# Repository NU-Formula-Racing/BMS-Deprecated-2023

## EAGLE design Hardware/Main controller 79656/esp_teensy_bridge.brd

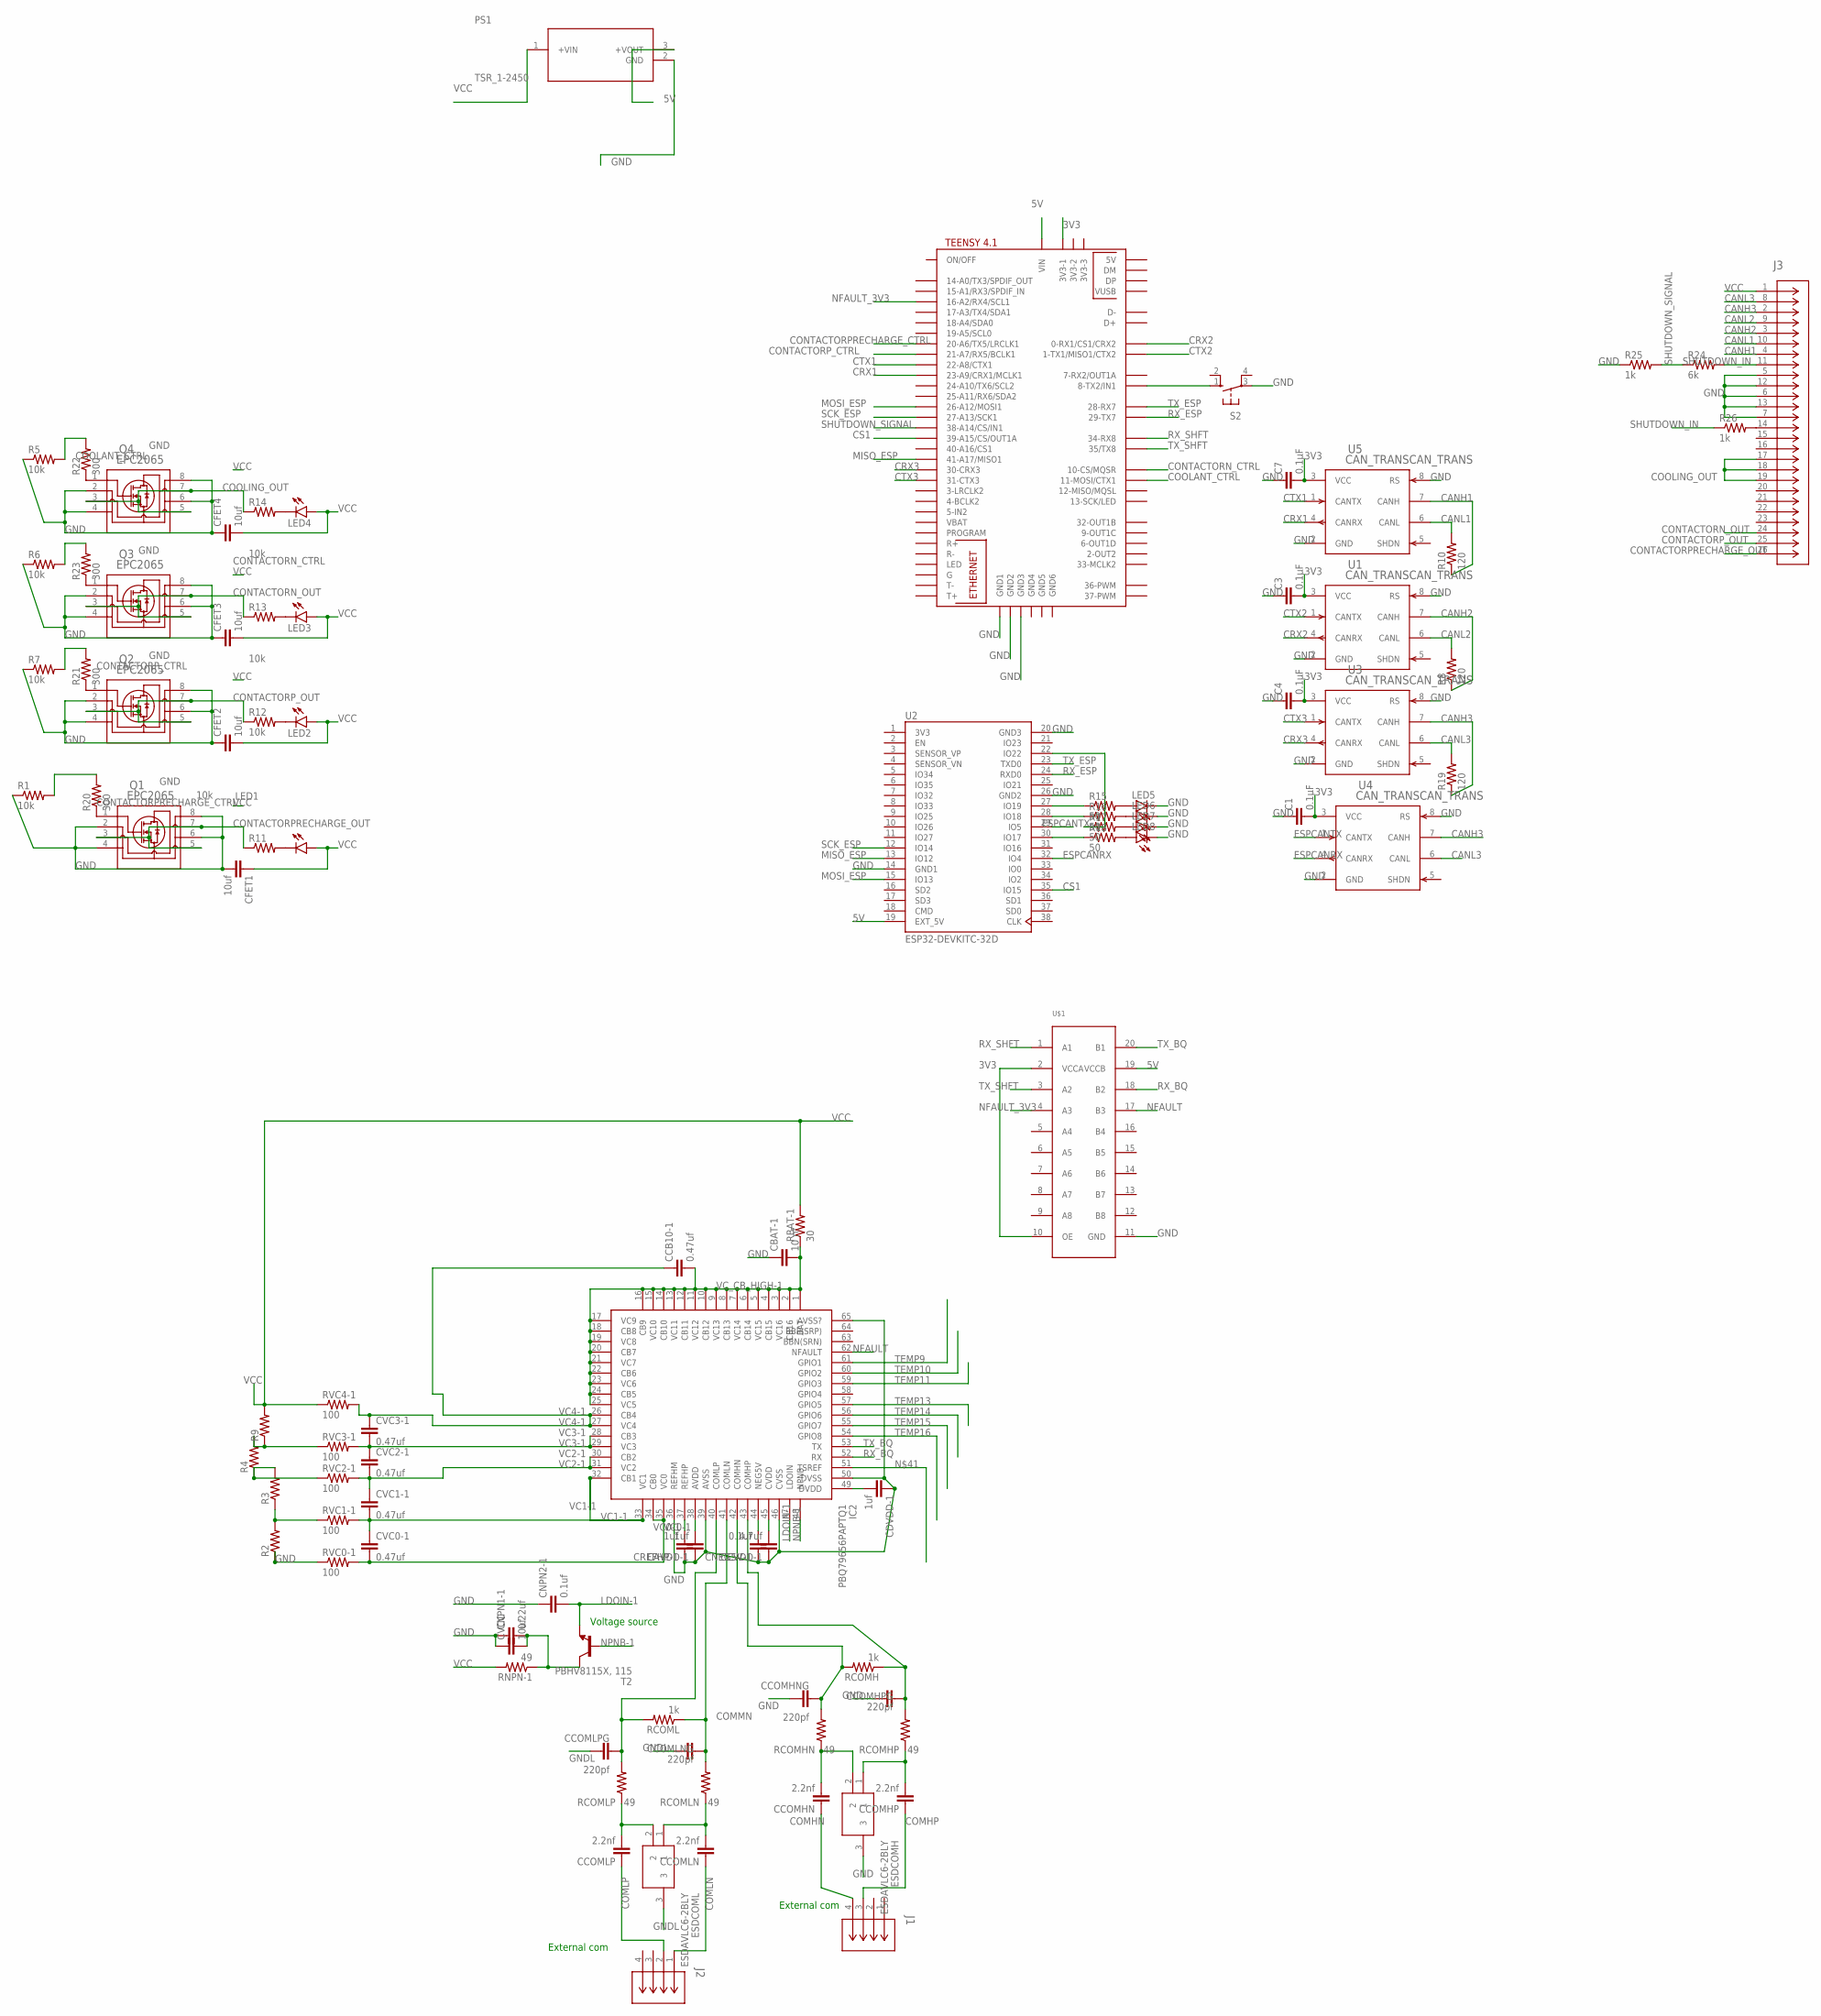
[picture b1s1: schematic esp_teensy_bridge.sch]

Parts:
C1, C3, C4, C7: 0.1μF; C0603
CAVDD-1: 1uf; C0603
CBAT-1: 10 nf; C0603
CCB10-1: 0.47uf; C0603
CCOMHN: 2.2nf; C075-032X103
CCOMHNG: 220pf; C0603
CCOMHP: 2.2nf; C075-032X103
CCOMHPG: 220pf; C0603
CCOMLN: 2.2nf; C075-032X103
CCOMLNG: 220pf; C0603
CCOMLP: 2.2nf; C075-032X103
CCOMLPG: 220pf; C0603
CCVDD-1: 4.7uf; C0603
CDVDD-1: 1uf; C0603
CFET1, CFET2, CFET3, CFET4: 10uf; C0805
CNEG5V-1: 0.1uf; C0603
CNPN1-1: 0.22uf; C0603
CNPN2-1: 0.1uf; C0603
CREFHP-1: 1uf; C0603
CVC0-1, CVC1-1, CVC2-1, CVC3-1: 0.47uf; C0603
CVCC: 10uf; C0805
ESDCOMH: ESDAVLC6-2BLY; SOT95P255X150-3N
ESDCOML: ESDAVLC6-2BLY; SOT95P255X150-3N
IC2: PBQ79656PAPTQ1; QFP50P1200X1200X120-65N
J1, J2: DF11-4DP-2DSA(24); CON4_2X2_UF_DF11_HIR
J3: TE_AMP_SURESEAL_26; CONN26_6473423-1_TEC
LED1, LED2, LED3, LED4, LED5, LED6, LED7, LED8: LEDSML0603; SML0603
PS1: TSR_1-2450; TSR1-SINGLE_TRP
Q1, Q2, Q3, Q4: EPC2065; EPC2065_ECC
R1, R5, R6, R7, R11, R12, R13, R14: 10k; R0603
R2, R3, R4, R9: R-US_R0805; R0805
R8, R10, R19: 120; R0603
R15, R16, R17, R18: 50; R0603
R20, R21, R22, R23: 300; R0603
R24: 6k; R0603
R25, R26: 1k; R0603
RBAT-1: 30; R0603
RCOMH: 1k; R0603
RCOMHN: 49; R0603
RCOMHP: 49; R0603
RCOML: 1k; R0603
RCOMLN: 49; R0603
RCOMLP: 49; R0603
RNPN-1: 49; R0603
RVC0-1, RVC1-1, RVC2-1, RVC3-1, RVC4-1: 100; R0603
S2: 10-XX; B3F-10XX
T2: PBHV8115X, 115; SOT89-BCE
U1, U3, U4, U5: CAN_TRANSCAN_TRANS; MAX3051ESA+
U2: ESP32-DEVKITC-32D; MODULE_ESP32-DEVKITC-32D
U$1: TXB0108PWSMD; TSSOP20
U$3: TEENSY41

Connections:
3V3: C1.2, C3.2, C4.2, C7.2, U1.3 (VCC), U2.1 (3V3), U3.3 (VCC), U4.3 (VCC), U5.3 (VCC), U$1.2 (VCCA), U$1.10 (OE), U$3.3V3-1
5V: PS1.3 (+VOUT), U2.19 (EXT_5V), U$1.19 (VCCB), U$3.VIN
CANH1: J3.4, R10.1, U5.7 (CANH)
CANH2: J3.3, R8.1, U1.7 (CANH)
CANH3: J3.2, R19.1, U3.7 (CANH), U4.7 (CANH)
CANL1: J3.10, R10.2, U5.6 (CANL)
CANL2: J3.9, R8.2, U1.6 (CANL)
CANL3: J3.8, R19.2, U3.6 (CANL), U4.6 (CANL)
COMHN: CCOMHN.1, J1.4
COMHP: CCOMHP.1, J1.3
COMLN: CCOMLN.1, J2.1
COMLP: CCOMLP.1, J2.2
CONTACTORN_CTRL: R6.2, R23.2, U$3.10-CS\MQSR (10-CS/MQSR)
CONTACTORN_OUT: J3.24, Q3.3, Q3.5, Q3.7, R13.1
CONTACTORPRECHARGE_CTRL: R1.2, R20.2, U$3.20-A6/TX5/LRCLK1
CONTACTORPRECHARGE_OUT: J3.26, Q1.3, Q1.5, Q1.7, R11.1
CONTACTORP_CTRL: R7.2, R21.2, U$3.21-A7/RX5/BCLK1
CONTACTORP_OUT: J3.25, Q2.3, Q2.5, Q2.7, R12.1
COOLANT_CTRL: R5.2, R22.2, U$3.11-MOSI/CTX1
COOLING_OUT: J3.17, J3.18, J3.19, Q4.3, Q4.5, Q4.7, R14.1
CRX1: U5.4 (CANRX), U$3.23-A9/CRX1/MCLK1
CRX2: U1.4 (CANRX), U$3.0-RX1/CS1/CRX2
CRX3: U3.4 (CANRX), U$3.30-CRX3
CS1: U2.35 (IO15), U$3.39-A15/CS/OUT1A
CTX1: U5.1 (CANTX), U$3.22-A8/CTX1
CTX2: U1.1 (CANTX), U$3.1-TX1/MISO1/CTX2
CTX3: U3.1 (CANTX), U$3.31-CTX3
CVDD-1: CCVDD-1.2, IC2.45 (CVDD)
ESPCANRX: U2.32 (IO4), U4.4 (CANRX)
ESPCANTX: U2.29 (IO5), U4.1 (CANTX)
GND: C1.1, C3.1, C4.1, C7.1, CAVDD-1.1, CBAT-1.1, CCOMHNG.1, CCOMHPG.1, CCVDD-1.1, CDVDD-1.1, CFET1.2, CFET2.1, CFET3.1, CFET4.1, CNEG5V-1.1, CNPN1-1.1, CNPN2-1.1, CREFHP-1.1, CVCC.1, ESDCOMH.3, IC2.36 (REFHM), IC2.39 (AVSS), IC2.46 (CVSS), IC2.50 (DVSS), IC2.65 (AVSS?), J3.5, J3.6, J3.7, J3.12, J3.13, LED5.C, LED6.C, LED7.C, LED8.C, PS1.2 (GND), Q1.2, Q1.4, Q1.6, Q1.8, Q2.2, Q2.4, Q2.6, Q2.8, Q3.2, Q3.4, Q3.6, Q3.8, Q4.2, Q4.4, Q4.6, Q4.8, R1.1, R2.1, R5.1, R6.1, R7.1, R25.1, RVC0-1.1, S2.3, U1.2 (GND), U1.8 (RS), U2.14 (GND1), U2.20 (GND3), U2.26 (GND2), U3.2 (GND), U3.8 (RS), U4.2 (GND), U4.8 (RS), U5.2 (GND), U5.8 (RS), U$1.11 (GND), U$3.GND1, U$3.GND2, U$3.GND3
GNDL: CCOMLNG.1, CCOMLPG.1, ESDCOML.3
LDOIN-1: CNPN2-1.2, IC2.47 (LDOIN), T2.E
MISO_ESP: U2.13 (IO12), U$3.41-A17/MISO1
MOSI_ESP: U2.15 (IO13), U$3.26-A12/MOSI1
unnamed: CCOMHP.2, ESDCOMH.1, RCOMHP.1
unnamed: J3.14, R26.2
unnamed: LED4.C, R14.2
unnamed: LED3.C, R13.2
unnamed: S2.1 (S), U$3.8-TX2/IN1
unnamed: CCOMHN.2, ESDCOMH.2, RCOMHN.1
unnamed: LED2.C, R12.2
unnamed: CCOMLNG.2, IC2.41 (COMLN), RCOML.1, RCOMLN.2
unnamed: R17.1, U2.22 (IO22)
unnamed: LED1.C, R11.2
unnamed: Q1.1, R20.1
unnamed: Q2.1, R21.1
unnamed: R15.1, U2.27 (IO19)
unnamed: R16.1, U2.28 (IO18)
unnamed: Q3.1, R23.1
unnamed: R18.1, U2.30 (IO17)
unnamed: LED5.A, R15.2
unnamed: LED6.A, R16.2
unnamed: LED7.A, R17.2
unnamed: LED8.A, R18.2
unnamed: Q4.1, R22.1
unnamed: CCOMLPG.2, IC2.40 (COMLP), RCOML.2, RCOMLP.2
unnamed: CCOMLP.2, ESDCOML.2, RCOMLP.1
unnamed: CCOMLN.2, ESDCOML.1, RCOMLN.1
unnamed: R3.2, R4.1, RVC2-1.1
unnamed: R2.2, R3.1, RVC1-1.1
unnamed: R4.2, R9.1, RVC3-1.1
unnamed: CREFHP-1.2, IC2.37 (REFHP)
unnamed: CAVDD-1.2, IC2.38 (AVDD)
unnamed: CNEG5V-1.2, IC2.44 (NEG5V)
unnamed: CDVDD-1.2, IC2.49 (DVDD)
unnamed: CNPN1-1.2, CVCC.2, RNPN-1.1, T2.C
unnamed: CCOMHPG.2, IC2.43 (COMHP), RCOMH.1, RCOMHP.2
unnamed: CCOMHNG.2, IC2.42 (COMHN), RCOMH.2, RCOMHN.2
NFAULT: IC2.62 (NFAULT), U$1.17 (B3)
NFAULT_3V3: U$1.4 (A3), U$3.16-A2/RX4/SCL1
NPNB-1: IC2.48 (NPNB), T2.B
RX_BQ: IC2.52 (RX), U$1.18 (B2)
RX_ESP: U2.24 (RXD0), U$3.29-TX7
RX_SHFT: U$1.1 (A1), U$3.34-RX8
SCK_ESP: U2.12 (IO14), U$3.27-A13/SCK1
SHUTDOWN_IN: J3.11, R24.2, R26.1
SHUTDOWN_SIGNAL: R24.1, R25.2, U$3.38-A14/CS/IN1
TEMP9: IC2.61 (GPIO1)
TEMP10: IC2.60 (GPIO2)
TEMP11: IC2.59 (GPIO3)
TEMP13: IC2.57 (GPIO5)
TEMP14: IC2.56 (GPIO6)
TEMP15: IC2.55 (GPIO7)
TEMP16: IC2.54 (GPIO8)
TX_BQ: IC2.53 (TX), U$1.20 (B1)
TX_ESP: U2.23 (TXD0), U$3.28-RX7
TX_SHFT: U$1.3 (A2), U$3.35-TX8 (35/TX8)
VC0-1: CVC0-1.2, IC2.34 (CB0), IC2.35 (VC0), RVC0-1.2
VC1-1: CVC0-1.1, CVC1-1.2, IC2.32 (CB1), IC2.33 (VC1), RVC1-1.2
VC2-1: CVC1-1.1, CVC2-1.2, IC2.30 (CB2), IC2.31 (VC2), RVC2-1.2
VC3-1: CVC2-1.1, CVC3-1.2, IC2.28 (CB3), IC2.29 (VC3), RVC3-1.2
VC4-1: CCB10-1.1, CVC3-1.1, IC2.26 (CB4), IC2.27 (VC4), RVC4-1.2
VCC: CFET1.1, CFET2.2, CFET3.2, CFET4.2, J3.1, LED1.A, LED2.A, LED3.A, LED4.A, PS1.1 (+VIN), R9.2, RBAT-1.2, RNPN-1.2, RVC4-1.1
VC_CB_HIGH-1: CBAT-1.2, CCB10-1.2, IC2.1 (BAT), IC2.2 (CB16), IC2.3 (VC16), IC2.4 (CB15), IC2.5 (VC15), IC2.6 (CB14), IC2.7 (VC14), IC2.8 (CB13), IC2.9 (VC13), IC2.10 (CB12), IC2.11 (VC12), IC2.12 (CB11), IC2.13 (VC11), IC2.14 (CB10), IC2.15 (VC10), IC2.16 (CB9), IC2.17 (VC9), IC2.18 (CB8), IC2.19 (VC8), IC2.20 (CB7), IC2.21 (VC7), IC2.22 (CB6), IC2.23 (VC6), IC2.24 (CB5), IC2.25 (VC5), RBAT-1.1

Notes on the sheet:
External com
Voltage source

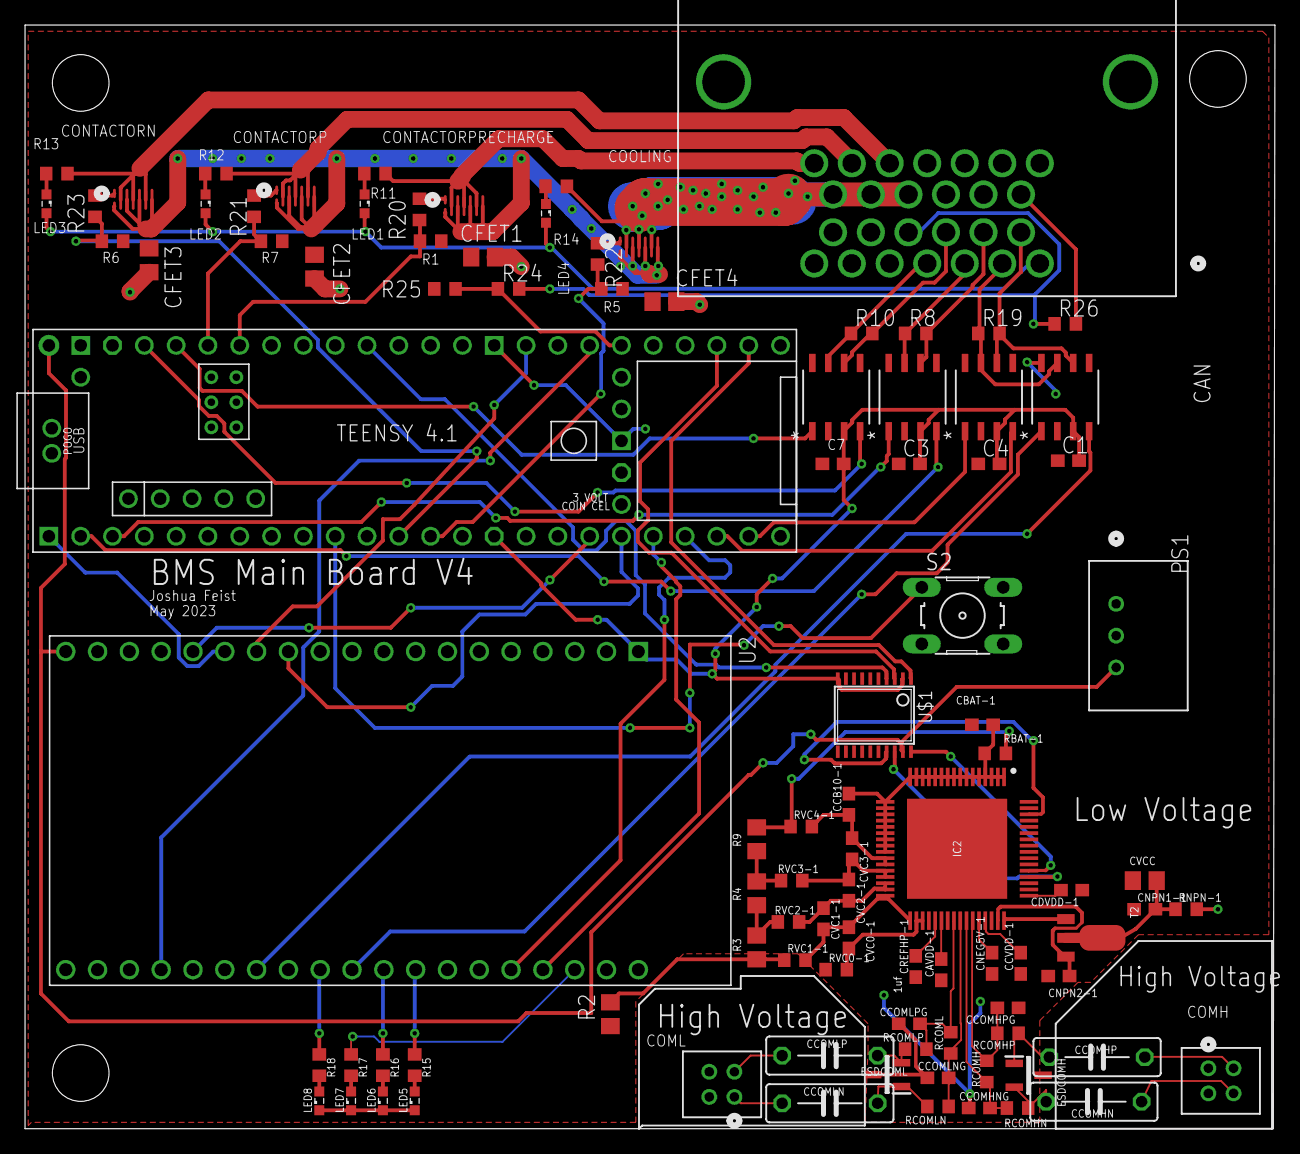
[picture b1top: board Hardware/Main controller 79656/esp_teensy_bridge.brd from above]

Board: 2 copper layers, 99.8 x 88.1 mm, 97 parts (0 on the bottom side), 88 nets.

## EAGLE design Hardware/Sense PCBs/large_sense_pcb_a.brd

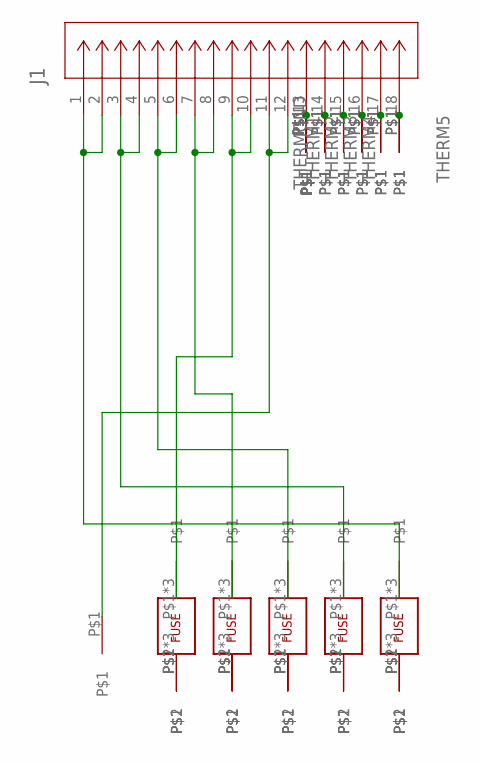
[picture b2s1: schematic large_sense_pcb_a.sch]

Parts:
J1: DF11-18DP-2DSA(24); CON18_2X9_UF_DF11_HIR
U$1, U$2, U$3, U$4, U$5: FUSE; FUSE_PADS
U$6, U$7, U$8, U$9, U$10, U$11: BB_CONTACT
U$12, U$13, U$14, U$15, U$16, U$17, U$18, U$19, U$20, U$21, U$22, U$23, U$24, U$25, U$26, U$27, U$28, U$29, U$30, U$31: THERM_PIN

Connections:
unnamed: J1.11, J1.12, U$11.P$1
unnamed: U$1.P$2, U$1.P$4, U$1.P$6, U$6.P$1
unnamed: J1.1, J1.2, U$5.P$1, U$5.P$3, U$5.P$5
unnamed: U$2.P$2, U$2.P$4, U$2.P$6, U$7.P$1
unnamed: U$5.P$2, U$5.P$4, U$5.P$6, U$10.P$1
unnamed: U$3.P$2, U$3.P$4, U$3.P$6, U$8.P$1
unnamed: J1.9, J1.10, U$1.P$1, U$1.P$3, U$1.P$5
unnamed: U$4.P$2, U$4.P$4, U$4.P$6, U$9.P$1
unnamed: J1.7, J1.8, U$2.P$1, U$2.P$3, U$2.P$5
unnamed: J1.5, J1.6, U$3.P$1, U$3.P$3, U$3.P$5
unnamed: J1.3, J1.4, U$4.P$1, U$4.P$3, U$4.P$5
THERM1: J1.14, U$22.P$1, U$23.P$1
THERM2: J1.15, U$24.P$1, U$25.P$1
THERM3: J1.16, U$26.P$1, U$27.P$1
THERM4: J1.17, U$28.P$1, U$29.P$1
THERM5: J1.18, U$30.P$1, U$31.P$1
THERMGND: J1.13, U$12.P$1, U$13.P$1, U$14.P$1, U$15.P$1, U$16.P$1, U$17.P$1, U$18.P$1, U$19.P$1, U$20.P$1, U$21.P$1

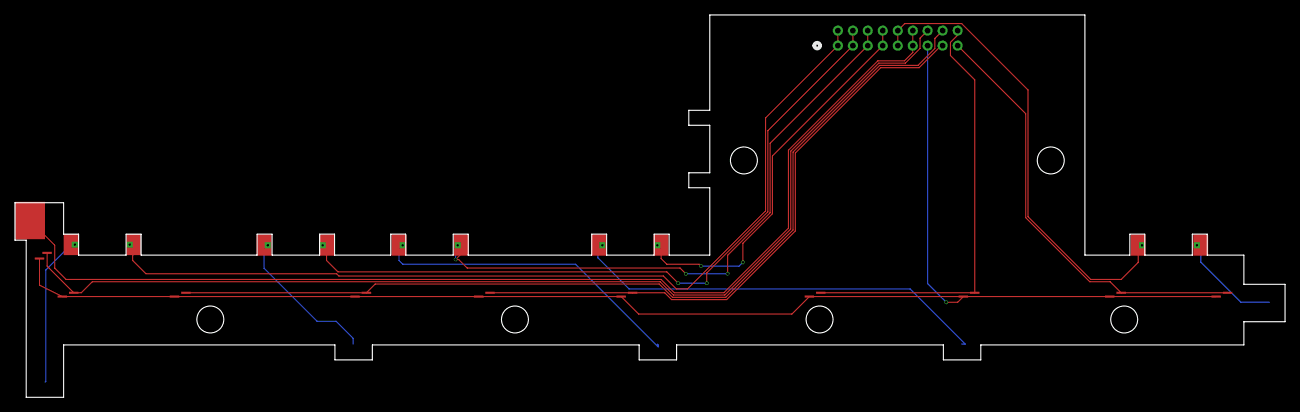
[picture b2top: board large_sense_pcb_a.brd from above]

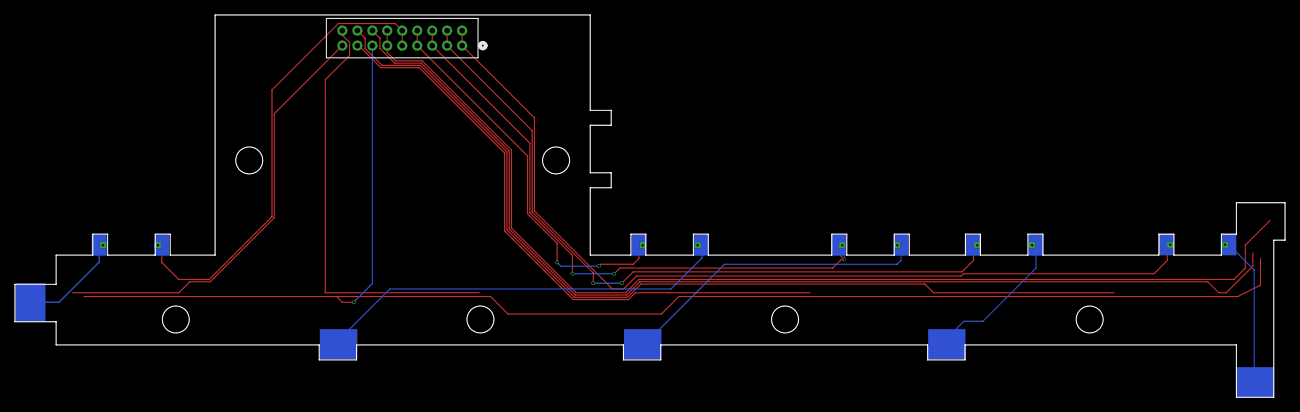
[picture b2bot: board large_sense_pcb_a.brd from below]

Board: 2 copper layers, 169.7 x 51.1 mm, 32 parts (6 on the bottom side), 17 nets.

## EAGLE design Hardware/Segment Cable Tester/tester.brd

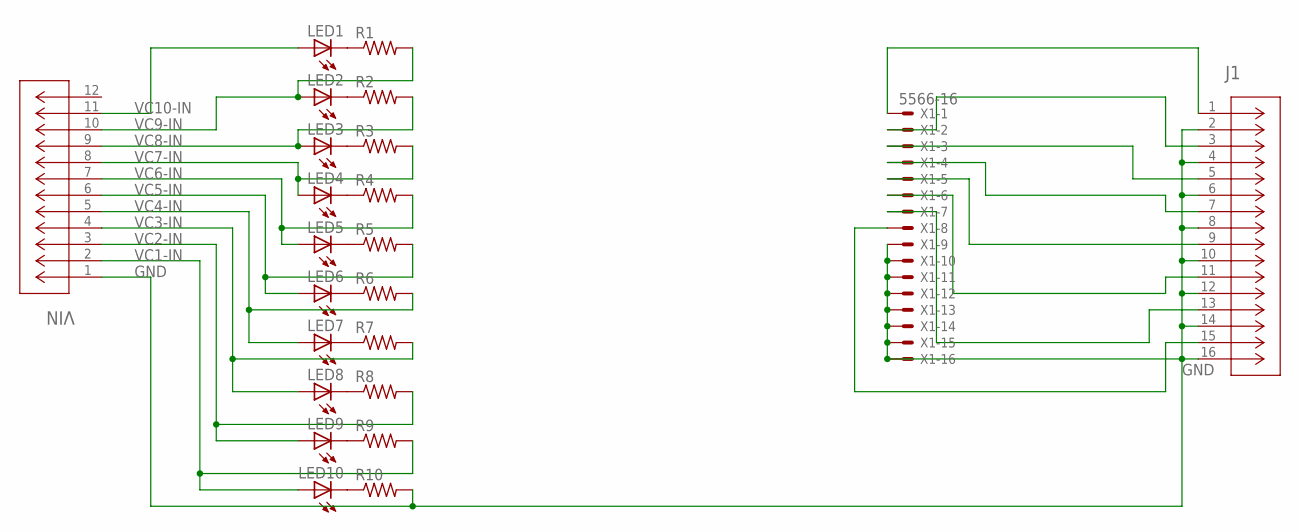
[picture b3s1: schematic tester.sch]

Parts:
J1: DF11-16DP-2DSA(01); CONN_DF11-16DP-2DSA(01)_HIR
LED1, LED2, LED3, LED4, LED5, LED6, LED7, LED8, LED9, LED10: LEDCHIPLED_0603; CHIPLED_0603
R1, R2, R3, R4, R5, R6, R7, R8, R9, R10: R-US_R0805; R0805
VIN: DF11-12DP-2DSA(01); CON12_2X6_UF_DF11_HIR
X1: 5566-16

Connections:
GND: J1.2, J1.4, J1.6, J1.8, J1.10, J1.12, J1.14, J1.16, R10.2, VIN.1, X1.9, X1.10, X1.11, X1.12, X1.13, X1.14, X1.15, X1.16
unnamed: LED2.C, R2.1
unnamed: LED3.C, R3.1
unnamed: LED5.C, R5.1
unnamed: LED6.C, R6.1
unnamed: LED7.C, R7.1
unnamed: LED8.C, R8.1
unnamed: LED9.C, R9.1
unnamed: LED10.C, R10.1
unnamed: LED1.C, R1.1
unnamed: LED4.C, R4.1
TEMP1: J1.1, X1.1
TEMP2: J1.3, X1.2
TEMP3: J1.5, X1.3
TEMP4: J1.7, X1.4
TEMP5: J1.9, X1.5
TEMP6: J1.11, X1.6
TEMP7: J1.13, X1.7
TEMP8: J1.15, X1.8
VC1-IN: LED10.A, R9.2, VIN.2
VC2-IN: LED9.A, R8.2, VIN.3
VC3-IN: LED8.A, R7.2, VIN.4
VC4-IN: LED7.A, R6.2, VIN.5
VC5-IN: LED6.A, R5.2, VIN.6
VC6-IN: LED5.A, R4.2, VIN.7
VC7-IN: LED4.A, R3.2, VIN.8
VC8-IN: LED3.A, R2.2, VIN.9
VC9-IN: LED2.A, R1.2, VIN.10
VC10-IN: LED1.A, VIN.11

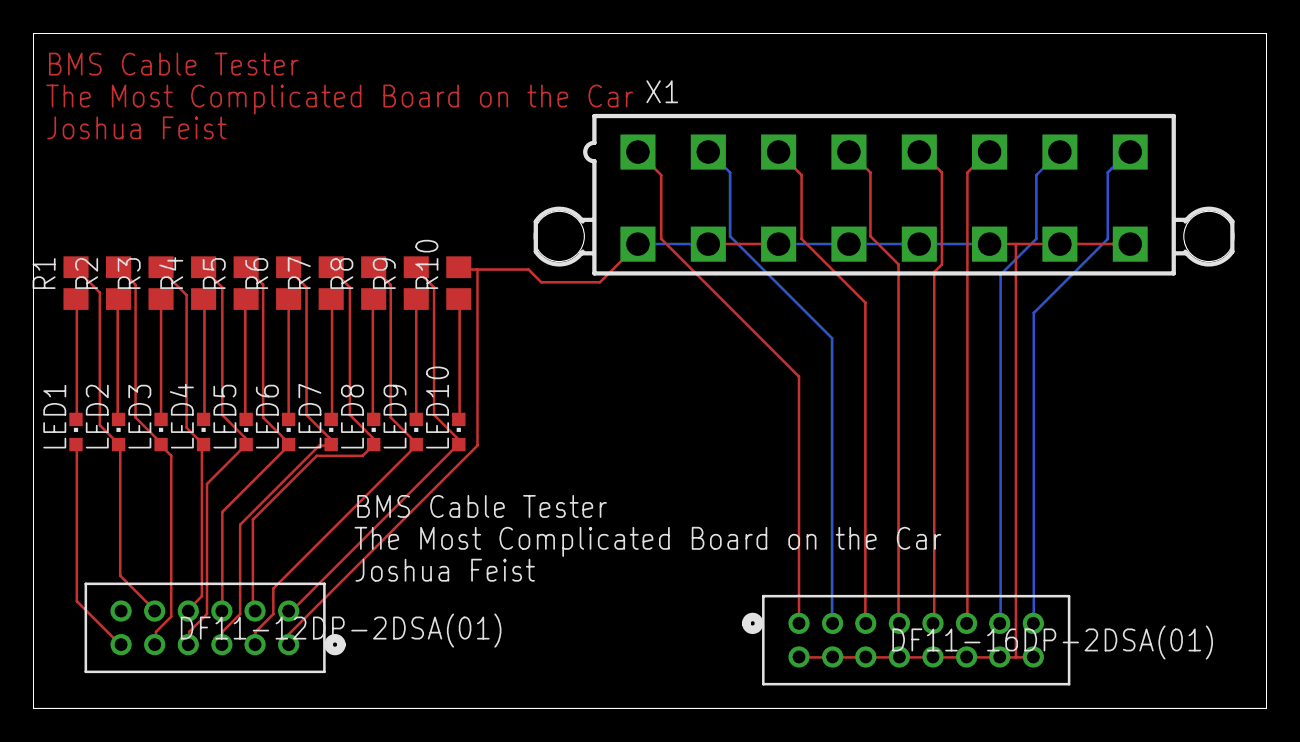
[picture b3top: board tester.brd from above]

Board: 2 copper layers, 73.6 x 40.3 mm, 23 parts (0 on the bottom side), 29 nets.

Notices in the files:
parts and their libraries:
COPYRIGHT: Copyright (C) 2023 Ultra Librarian. All rights reserved.
COPYRIGHT: Copyright (C) 2022 Ultra Librarian. All rights reserved.
